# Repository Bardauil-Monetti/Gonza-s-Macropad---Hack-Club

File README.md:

Gonza's Macropad:

This is my first proyect for hack club, I hope you like it.

Description:

A simple macropad for gaming, all 6 keycaps and the encoder have diferent characters combinations to use in discord or in game configuration.

## BOM

- 6× Cherry MX Switches
- 6× SK6812 MINI LEDs
- 1× XIAO RP2040
- 6× Blank DSA Keycaps
- 4× M3×16 Bolts
- 4× M3 Heatset Inserts

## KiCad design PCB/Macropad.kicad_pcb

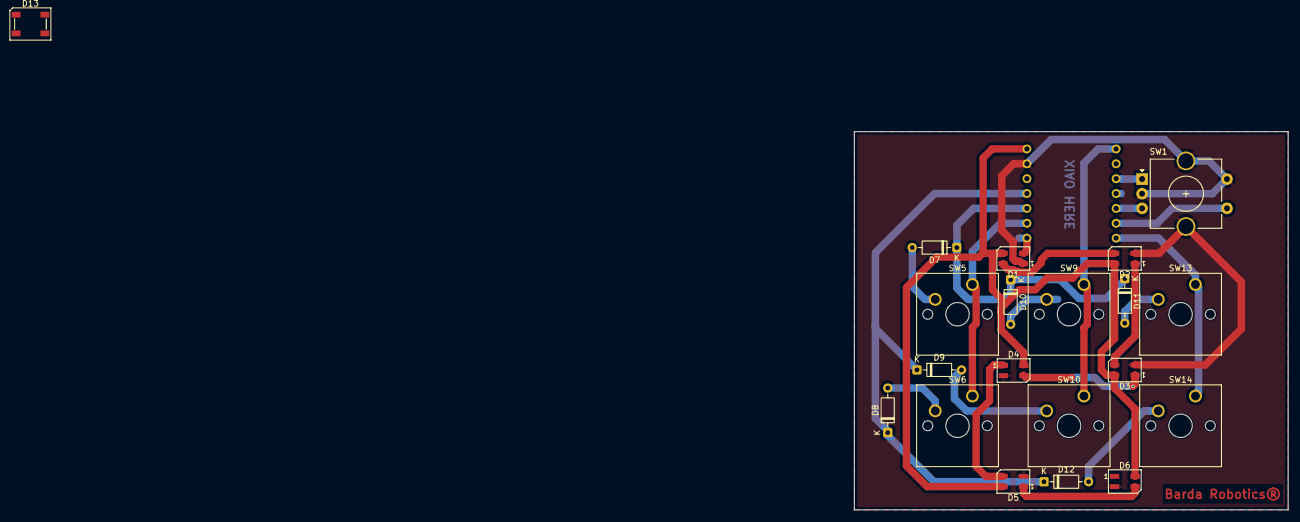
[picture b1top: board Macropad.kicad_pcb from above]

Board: 2 copper layers, 74.1 x 64.6 mm, 21 parts (1 on the bottom side), 22 nets.

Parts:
D1: SK6812; LED_SK6812MINI_PLCC4_3.5x3.5mm_P1.75mm
D2, D3, D4, D5, D6: SK6812MINI; LED_SK6812MINI_PLCC4_3.5x3.5mm_P1.75mm
D7, D8, D9, D10, D11, D12: 1N4148; D_DO-35_SOD27_P7.62mm_Horizontal
D13: SK6812; LED_SK6812_PLCC4_5.0x5.0mm_P3.2mm
SW1: RotaryEncoder_Switch_MP; RotaryEncoder_Alps_EC11E-Switch_Vertical_H20mm_CircularMoun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
SW5, SW6, SW9, SW10, SW13, SW14: SW_Push; SW_Cherry_MX_1.00u_PCB
U1: XIAO-RP2040-DIP

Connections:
+5V: D1.3 (VDD), D2.4 (VDD), D3.4 (VDD), D4.4 (VDD), D5.4 (VDD), D6.4 (VDD), U1.14 (VBUS)
A: SW1.A, U1.3 (GPIO28/ADC2/A2)
B: SW1.B, U1.5 (GPIO6/SDA)
C1: SW13.1, SW14.1, U1.7 (GPIO0/TX)
C2: SW9.1, SW10.1, U1.1 (GPIO26/ADC0/A0)
C3: SW5.1, SW6.1, U1.9 (GPIO2/SCK)
F1: D7.1 (K), D10.1 (K), D11.1 (K), U1.10 (GPIO4/MISO)
F2: D8.1 (K), D9.1 (K), D12.1 (K), U1.11 (GPIO3/MOSI)
GND: D1.1 (VSS), D2.2 (VSS), D3.2 (VSS), D4.2 (VSS), D5.2 (VSS), D6.2 (VSS), SW1.C, SW1.MP, SW1.S2, U1.13 (GND)
LEDs: D1.2 (DIN), U1.8 (GPIO1/RX)
unnamed: D1.4 (DOUT), D2.3 (DIN)
unnamed: D2.1 (DOUT), D3.3 (DIN)
unnamed: D3.1 (DOUT), D4.3 (DIN)
unnamed: D4.1 (DOUT), D5.3 (DIN)
unnamed: D5.1 (DOUT), D6.3 (DIN)
unnamed: D7.2 (A), SW5.2
unnamed: D8.2 (A), SW6.2
unnamed: D9.2 (A), SW10.2
unnamed: D10.2 (A), SW9.2
unnamed: D11.2 (A), SW13.2
unnamed: D12.2 (A), SW14.2
unnamed: SW1.S1, U1.6 (GPIO7/SCL)

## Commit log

2026-01-17 Add files via upload
    Initial commit
2026-01-17 Update README with images and formatting fixes
    Added images and corrected formatting in the README.
2026-01-17 Fix formatting and update README content
2026-01-17 Format README.md for better readability
2026-01-17 Fix formatting and BOM details in README.md
    Updated formatting and corrected BOM section.
2026-01-23 Fixed version of the PCB
2026-01-26 Primer commit
